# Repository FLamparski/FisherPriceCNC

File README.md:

# Fisher Price CNC

A desktop, 2D CNC machine made from parts salvaged from a
really terrible 3D priner. This repository contains the
phyiscal CAD design of the machine, electrical and electronic
schematics for any custom boards, and any extra code to make it
run (unlikely to be needed but you never know).

More documentation is currently available on the following
Trello board: https://trello.com/b/17SHQEqY/fisher-price-cnc

## Physical designs - OpenSCAD  - `/scad`

The machine is designed with OpenSCAD, a CAD program that does
away with all of this "drawing" nonsense and instead lets you
use a C-ish programming language to do geometry. The upshot
is that you could treat it like any old source file in git, and
you also have a fairly well understood model for including
libraries.

Speaking of libraries, you will need them. Please install the
following to your OpenSCAD libraries folder:

* [NopSCADlib](https://github.com/nophead/NopSCADlib)

### Assembly instructions

The project leverages NopSCADlib's autogenerated assembly instructions and asset generation. The
instructions are in [`ASSEMBLY.md`](ASSEMBLY.md). Note that these might be a bit variable in quality,
please open an issue if something's not clear. I intend on creating more detailed instructions
towards the end of the project.

To regenerate the assembly instructions, STLs, images, and the bill of materials, use `make_all.ps1`.

## Firmware

This machine uses GRBL v1.1 as its firmware. There is a configuration file, `grbl_config.h`, that is
required to compile and upload GRBL and have it work correctly - it needs to disable homing on the
Z axis because the Z axis does not exist.

Copy the `grbl_config.h` on top of the `config.h` in whatever location you have installed GRBL,
and then reflash through the Arduino IDE.

## Attribution

A number of the parts and a lot of the code for this machine
has been borrowed from other projects. Here's a list:

* Some phyiscal parts have been reused or adapted from the [Prusa i3 MK3s](https://github.com/prusa3d/Original-Prusa-i3/tree/MK3S/Printed-Parts/SCAD) (GPLv3)
* [GRBL](https://github.com/gnea/grbl) is currently used as firmware (GPLv3)

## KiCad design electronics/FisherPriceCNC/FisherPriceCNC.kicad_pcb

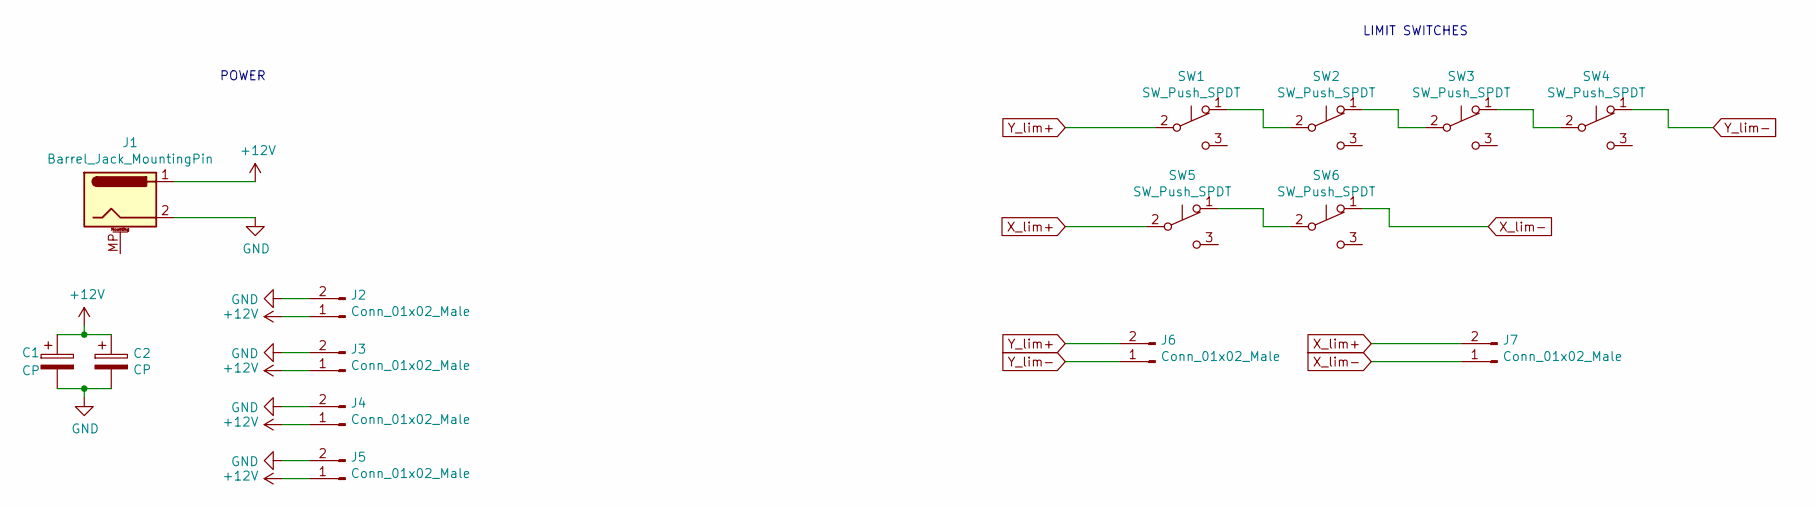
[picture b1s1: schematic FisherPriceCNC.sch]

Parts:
C1, C2: CP; CP_Radial_D5.0mm_P2.50mm
J1: Barrel_Jack_MountingPin; BarrelJack_Horizontal
J2, J3, J4, J5, J6, J7: Conn_01x02_Male; PinHeader_1x02_P2.54mm_Vertical
SW1, SW2, SW3, SW4, SW5, SW6: SW_Push_SPDT; PinHeader_1x02_P2.54mm_Vertical

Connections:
+12V: C1.1, C2.1, J1.1, J2.1, J3.1, J4.1, J5.1
GND: C1.2, C2.2, J1.2, J2.2, J3.2, J4.2, J5.2
unnamed: SW1.1 (A), SW2.2 (B)
unnamed: SW2.1 (A), SW3.2 (B)
unnamed: SW3.1 (A), SW4.2 (B)
unnamed: SW5.1 (A), SW6.2 (B)
X_lim+: J7.2, SW5.2 (B)
X_lim-: J7.1, SW6.1 (A)
Y_lim+: J6.2, SW1.2 (B)
Y_lim-: J6.1, SW4.1 (A)

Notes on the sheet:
POWER
LIMIT SWITCHES

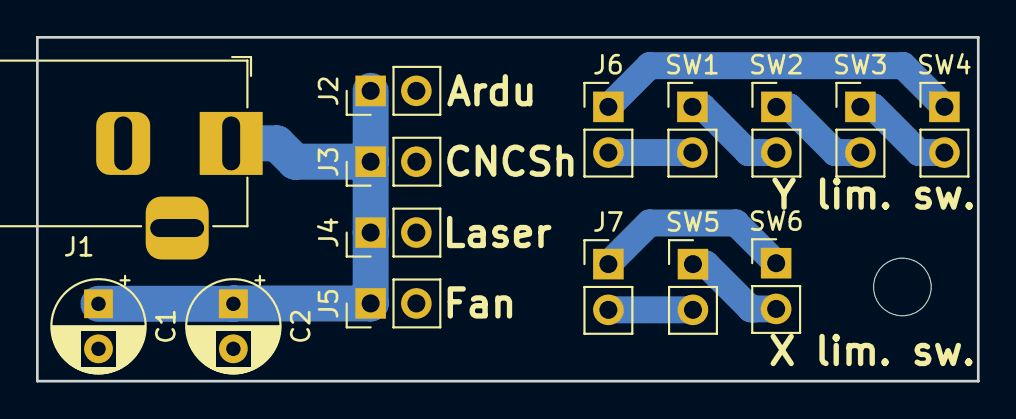
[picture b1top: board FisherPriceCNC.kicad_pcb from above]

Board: 2 copper layers, 52.3 x 19.1 mm, 15 parts (0 on the bottom side), 10 nets.

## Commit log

2020-03-08 Make BOM/assembly instructions generation work
2020-03-14 Y-axis motor mounting brackets v1
2020-03-14 Improve nopscadlib tooling
2020-03-14 Update automatically generated files
2020-03-14 Add y-idlers and belts
2020-03-14 Docs+stls: y axis idler
2020-03-15 WIP y-carriage
2020-03-15 Update the base y-carriage and docs
2020-03-21 Don't do MPMD belts
2020-03-21 Update to built model
2020-03-21 Update STLs and docs
2020-03-21 Add constraints for rods
2020-03-21 Add limit switches for the y-axis
2020-03-21 Update docs for limit switches
2020-03-22 Rearrange assemblies to generate saner docs (fix #2)
2020-03-28 Use M4 screws for y-idlers
2020-03-29 WIP x-axis gantry
2020-04-05 Add the x-carriage and laser module assembly
2020-04-10 Add GRBL config for an XY-only machine
2020-04-11 Wire holder for the x-axis
2020-04-25 Electronics box
2020-04-25 Update docs
